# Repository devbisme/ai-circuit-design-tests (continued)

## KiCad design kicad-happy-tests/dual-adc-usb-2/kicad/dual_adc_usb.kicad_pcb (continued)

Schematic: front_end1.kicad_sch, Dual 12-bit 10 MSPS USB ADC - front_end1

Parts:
C32: 15pF; C_1206_3216Metric; MPN GRM3195C2A150JA01D
C33: 2.2pF; C_1206_3216Metric; MPN GRM3195C2A2R2CA01D
C34: 10pF; C_0603_1608Metric; MPN GRM1885C1H100JA01D
C35: 3-10pF; C_Trimmer_Murata_TZC3; MPN TZC3Z100A110R00
C36, C38, C42: 100nF; C_0603_1608Metric; MPN GRM188R71C104KA01D
C37, C39, C43: 1uF; C_0603_1608Metric; MPN GRM188R71C105KA12D
C40, C41: 22pF; C_0603_1608Metric; MPN GRM1885C1H220JA01D
C44: 330pF; C_0603_1608Metric; MPN GRM1885C1H331JA01D
D2: BAV99; SOT-23; MPN BAV99
J2: IN_A; BNC_Amphenol_B6252HB-NPP3G-50_Horizontal; MPN B6252HB-NPP3G-50
R19: 909k; R_1206_3216Metric; Tolerance 0.1%; MPN RT1206BRD07909KL
R20: 100k; R_0603_1608Metric; Tolerance 0.1%; MPN RT0603BRD07100KL
R21: 100; R_0603_1608Metric; Tolerance 1%; MPN RC0603FR-07100RL
R22, R23: 1k; R_0603_1608Metric; Tolerance 0.1%; MPN RT0603BRD071KL
R24, R25: 953; R_0603_1608Metric; Tolerance 0.1%; MPN RT0603BRD07953RL
R26, R27: 49.9; R_0603_1608Metric; Tolerance 1%; MPN RC0603FR-0749R9L
U8: OPA810xD; SOIC-8_3.9x4.9mm_P1.27mm; MPN OPA810IDR
U9: THS4521ID; SOIC-8_3.9x4.9mm_P1.27mm; MPN THS4521IDR

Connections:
+3V3A: C36.1, C37.1, D2.2 (A), U8.7 (V+); also elsewhere on the board
+3V3_ADC: C42.1, C43.1, U9.3 (V_{S+}), U9.7 (~PD); also elsewhere on the board
-3V3A: C38.1, C39.1, D2.1 (K), U8.4 (V-); also elsewhere on the board
/front_end1/ATT_A: C33.2, C34.1, C35.1, D2.3 (K), R19.2, R20.1, R21.1
/front_end1/BUF_IN_A: R21.2, U8.3 (+)
/front_end1/BUF_OUT_A: R22.1, U8.2 (-), U8.6
/front_end1/FDA_INN_A: C41.1, R23.2, R25.1, U9.1 (-)
/front_end1/FDA_INP_A: C40.1, R22.2, R24.1, U9.8 (+)
/front_end1/FDA_OUTN_A: C40.2, R24.2, R27.1, U9.5
/front_end1/FDA_OUTP_A: C41.2, R25.2, R26.1, U9.4
/front_end1/VIN_A: C32.1, C33.1, J2.1 (In), R19.1
AIN_AN: C44.2, R27.2; also elsewhere on the board
AIN_AP: C44.1, R26.2; also elsewhere on the board
GND: C32.2, C34.2, C35.2, C36.2, C37.2, C38.2, C39.2, C42.2, C43.2, J2.2 (Ext), R20.2, R23.1, U9.6 (V_{S-}); also elsewhere on the board
VCMA: U9.2 (V_{OCM}); also elsewhere on the board

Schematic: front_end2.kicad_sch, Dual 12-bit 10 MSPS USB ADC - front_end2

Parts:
C45: 15pF; C_1206_3216Metric; MPN GRM3195C2A150JA01D
C46: 2.2pF; C_1206_3216Metric; MPN GRM3195C2A2R2CA01D
C47: 10pF; C_0603_1608Metric; MPN GRM1885C1H100JA01D
C48: 3-10pF; C_Trimmer_Murata_TZC3; MPN TZC3Z100A110R00
C49, C51, C55: 100nF; C_0603_1608Metric; MPN GRM188R71C104KA01D
C50, C52, C56: 1uF; C_0603_1608Metric; MPN GRM188R71C105KA12D
C53, C54: 22pF; C_0603_1608Metric; MPN GRM1885C1H220JA01D
C57: 330pF; C_0603_1608Metric; MPN GRM1885C1H331JA01D
D3: BAV99; SOT-23; MPN BAV99
J3: IN_B; BNC_Amphenol_B6252HB-NPP3G-50_Horizontal; MPN B6252HB-NPP3G-50
R28: 909k; R_1206_3216Metric; Tolerance 0.1%; MPN RT1206BRD07909KL
R29: 100k; R_0603_1608Metric; Tolerance 0.1%; MPN RT0603BRD07100KL
R30: 100; R_0603_1608Metric; Tolerance 1%; MPN RC0603FR-07100RL
R31, R32: 1k; R_0603_1608Metric; Tolerance 0.1%; MPN RT0603BRD071KL
R33, R34: 953; R_0603_1608Metric; Tolerance 0.1%; MPN RT0603BRD07953RL
R35, R36: 49.9; R_0603_1608Metric; Tolerance 1%; MPN RC0603FR-0749R9L
U10: OPA810xD; SOIC-8_3.9x4.9mm_P1.27mm; MPN OPA810IDR
U11: THS4521ID; SOIC-8_3.9x4.9mm_P1.27mm; MPN THS4521IDR

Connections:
+3V3A: C49.1, C50.1, D3.2 (A), U10.7 (V+); also elsewhere on the board
+3V3_ADC: C55.1, C56.1, U11.3 (V_{S+}), U11.7 (~PD); also elsewhere on the board
-3V3A: C51.1, C52.1, D3.1 (K), U10.4 (V-); also elsewhere on the board
/front_end2/ATT_B: C46.2, C47.1, C48.1, D3.3 (K), R28.2, R29.1, R30.1
/front_end2/BUF_IN_B: R30.2, U10.3 (+)
/front_end2/BUF_OUT_B: R31.1, U10.2 (-), U10.6
/front_end2/FDA_INN_B: C54.1, R32.2, R34.1, U11.1 (-)
/front_end2/FDA_INP_B: C53.1, R31.2, R33.1, U11.8 (+)
/front_end2/FDA_OUTN_B: C53.2, R33.2, R36.1, U11.5
/front_end2/FDA_OUTP_B: C54.2, R34.2, R35.1, U11.4
/front_end2/VIN_B: C45.1, C46.1, J3.1 (In), R28.1
AIN_BN: C57.2, R36.2; also elsewhere on the board
AIN_BP: C57.1, R35.2; also elsewhere on the board
GND: C45.2, C47.2, C48.2, C49.2, C50.2, C51.2, C52.2, C55.2, C56.2, J3.2 (Ext), R29.2, R32.1, U11.6 (V_{S-}); also elsewhere on the board
VCMB: U11.2 (V_{OCM}); also elsewhere on the board

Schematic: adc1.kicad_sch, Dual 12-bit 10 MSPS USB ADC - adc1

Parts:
C58, C59: 2.2uF; C_0603_1608Metric; MPN GRM188R61C225KE15D
C60, C64, C68, C69, C70, C71, C73, C74: 100nF; C_0603_1608Metric; MPN GRM188R71C104KA01D
C61, C65: 2.2uF; C_0805_2012Metric; MPN GRM21BR71C225KA12L
C62, C63, C66, C67: 1uF; C_0603_1608Metric; MPN GRM188R71C105KA12D
C72: 10uF; C_0805_2012Metric; MPN GRM21BR61C106KE15L
R37: 20k; R_0603_1608Metric; Tolerance 1%; MPN RC0603FR-0720KL
R38, R39: 10k; R_0603_1608Metric; Tolerance 1%; MPN RC0603FR-0710KL
U12: LTC2291IUP; QFN-64-1EP_9x9mm_P0.5mm_EP7.15x7.15mm; MPN LTC2291IUP#PBF

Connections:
+3V3: C73.1, C74.1, U12.32 (OVDD), U12.49 (OVDD); also elsewhere on the board
+3V3_ADC: C68.1, C69.1, C70.1, C71.1, C72.1, R37.1, U12.7 (VDD), U12.10 (VDD), U12.18 (VDD), U12.19 (SENSEB), U12.21 (MUX), U12.62 (SENSEA), U12.63 (VDD); also elsewhere on the board
/adc1/ADC_MODE: R37.2, R38.1, U12.60 (MODE)
/adc1/REFHA: C60.1, C61.1, C62.1, U12.3 (REFHA), U12.4 (REFHA)
/adc1/REFHB: C64.1, C65.1, C66.1, U12.13 (REFHB), U12.14 (REFHB)
/adc1/REFLA: C60.2, C61.2, C63.1, U12.5 (REFLA), U12.6 (REFLA)
/adc1/REFLB: C64.2, C65.2, C67.1, U12.11 (REFLB), U12.12 (REFLB)
ADC_CLK: U12.8 (CLKA), U12.9 (CLKB); also elsewhere on the board
ADC_SHDN: R39.1, U12.22 (SHDNB), U12.59 (SHDNA); also elsewhere on the board
AIN_AN: U12.2 (AINA-); also elsewhere on the board
AIN_AP: U12.1 (AINA+); also elsewhere on the board
AIN_BN: U12.15 (AINB-); also elsewhere on the board
AIN_BP: U12.16 (AINB+); also elsewhere on the board
DA0: U12.43 (DA0); also elsewhere on the board
DA1: U12.44 (DA1); also elsewhere on the board
DA2: U12.45 (DA2); also elsewhere on the board
DA3: U12.46 (DA3); also elsewhere on the board
DA4: U12.47 (DA4); also elsewhere on the board
DA5: U12.48 (DA5); also elsewhere on the board
DA6: U12.51 (DA6); also elsewhere on the board
DA7: U12.52 (DA7); also elsewhere on the board
DA8: U12.53 (DA8); also elsewhere on the board
DA9: U12.54 (DA9); also elsewhere on the board
DA10: U12.55 (DA10); also elsewhere on the board
DA11: U12.56 (DA11); also elsewhere on the board
DB0: U12.26 (DB0); also elsewhere on the board
DB1: U12.27 (DB1); also elsewhere on the board
DB2: U12.28 (DB2); also elsewhere on the board
DB3: U12.29 (DB3); also elsewhere on the board
DB4: U12.30 (DB4); also elsewhere on the board
DB5: U12.33 (DB5); also elsewhere on the board
DB6: U12.34 (DB6); also elsewhere on the board
DB7: U12.35 (DB7); also elsewhere on the board
DB8: U12.36 (DB8); also elsewhere on the board
DB9: U12.37 (DB9); also elsewhere on the board
DB10: U12.38 (DB10); also elsewhere on the board
DB11: U12.39 (DB11); also elsewhere on the board
GND: C58.2, C59.2, C62.2, C63.2, C66.2, C67.2, C68.2, C69.2, C70.2, C71.2, C72.2, C73.2, C74.2, R38.2, R39.2, U12.17 (GND), U12.23 (~OEB), U12.31 (OGND), U12.50 (OGND), U12.58 (~OEA), U12.64 (GND), U12.65 (GND); also elsewhere on the board
OFA: U12.57 (OFA); also elsewhere on the board
OFB: U12.40 (OFB); also elsewhere on the board
VCMA: C58.1, U12.61 (VCMA); also elsewhere on the board
VCMB: C59.1, U12.20 (VCMB); also elsewhere on the board

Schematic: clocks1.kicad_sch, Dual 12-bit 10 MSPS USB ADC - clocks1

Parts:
C75, C76: 100nF; C_0603_1608Metric; MPN GRM188R71C104KA01D
R40: 22; R_0603_1608Metric; Tolerance 1%; MPN RC0603FR-0722RL
R41, R42: 33; R_0603_1608Metric; Tolerance 1%; MPN RC0603FR-0733RL
Y2: 10MHz; Oscillator_SMD_Abracon_ASE-4Pin_3.2x2.5mm; MPN ASE-10.000MHZ-LC-T
Y3: 25MHz; Oscillator_SMD_Abracon_ASE-4Pin_3.2x2.5mm; MPN ASE-25.000MHZ-LC-T

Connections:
+3V3: C75.1, C76.1, Y2.1 (EN), Y2.4 (Vdd), Y3.1 (EN), Y3.4 (Vdd); also elsewhere on the board
/clocks1/XO10_OUT: R40.1, R41.1, Y2.3 (OUT)
/clocks1/XO25_OUT: R42.1, Y3.3 (OUT)
ADC_CLK: R40.2; also elsewhere on the board
FPGA_ADC_CLK: R41.2; also elsewhere on the board
GND: C75.2, C76.2, Y2.2 (GND), Y3.2 (GND); also elsewhere on the board
SYSCLK: R42.2; also elsewhere on the board

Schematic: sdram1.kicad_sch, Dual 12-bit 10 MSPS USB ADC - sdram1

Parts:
C77, C78, C79, C80, C81, C82, C83: 100nF; C_0603_1608Metric; MPN GRM188R71C104KA01D
C84: 10uF; C_0805_2012Metric; MPN GRM21BR61C106KE15L
U13: IS42S16400J-7TL; TSOP-II-54_22.2x10.16mm_P0.8mm; MPN IS42S16400J-7TL

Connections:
+3V3: C77.1, C78.1, C79.1, C80.1, C81.1, C82.1, C83.1, C84.1, U13.1 (VDD), U13.3 (VDDQ), U13.9 (VDDQ), U13.14 (VDD), U13.27 (VDD), U13.43 (VDDQ), U13.49 (VDDQ); also elsewhere on the board
GND: C77.2, C78.2, C79.2, C80.2, C81.2, C82.2, C83.2, C84.2, U13.6 (GNDQ), U13.12 (GNDQ), U13.28 (GND), U13.41 (GND), U13.46 (GNDQ), U13.52 (GNDQ), U13.54 (GND); also elsewhere on the board
SD_A0: U13.23 (A0); also elsewhere on the board
SD_A1: U13.24 (A1); also elsewhere on the board
SD_A2: U13.25 (A2); also elsewhere on the board
SD_A3: U13.26 (A3); also elsewhere on the board
SD_A4: U13.29 (A4); also elsewhere on the board
SD_A5: U13.30 (A5); also elsewhere on the board
SD_A6: U13.31 (A6); also elsewhere on the board
SD_A7: U13.32 (A7); also elsewhere on the board
SD_A8: U13.33 (A8); also elsewhere on the board
SD_A9: U13.34 (A9); also elsewhere on the board
SD_A10: U13.22 (A10); also elsewhere on the board
SD_A11: U13.35 (A11); also elsewhere on the board
SD_BA0: U13.20 (BA0); also elsewhere on the board
SD_BA1: U13.21 (BA1); also elsewhere on the board
SD_CAS_N: U13.17 (~CAS); also elsewhere on the board
SD_CKE: U13.37 (CKE); also elsewhere on the board
SD_CLK: U13.38 (CLK); also elsewhere on the board
SD_CS_N: U13.19 (~CS); also elsewhere on the board
SD_DQ0: U13.2 (DQ0); also elsewhere on the board
SD_DQ1: U13.4 (DQ1); also elsewhere on the board
SD_DQ2: U13.5 (DQ2); also elsewhere on the board
SD_DQ3: U13.7 (DQ3); also elsewhere on the board
SD_DQ4: U13.8 (DQ4); also elsewhere on the board
SD_DQ5: U13.10 (DQ5); also elsewhere on the board
SD_DQ6: U13.11 (DQ6); also elsewhere on the board
SD_DQ7: U13.13 (DQ7); also elsewhere on the board
SD_DQ8: U13.42 (DQ8); also elsewhere on the board
SD_DQ9: U13.44 (DQ9); also elsewhere on the board
SD_DQ10: U13.45 (DQ10); also elsewhere on the board
SD_DQ11: U13.47 (DQ11); also elsewhere on the board
SD_DQ12: U13.48 (DQ12); also elsewhere on the board
SD_DQ13: U13.50 (DQ13); also elsewhere on the board
SD_DQ14: U13.51 (DQ14); also elsewhere on the board
SD_DQ15: U13.53 (DQ15); also elsewhere on the board
SD_DQMH: U13.39 (UDQM); also elsewhere on the board
SD_DQML: U13.15 (LDQM); also elsewhere on the board
SD_RAS_N: U13.18 (~RAS); also elsewhere on the board
SD_WE_N: U13.16 (~WE); also elsewhere on the board

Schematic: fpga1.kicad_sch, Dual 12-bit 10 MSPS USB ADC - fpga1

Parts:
C85, C86, C87, C88, C90, C91, C92, C93, C94, C95, C96, C97, C101, C103, C104: 100nF; C_0603_1608Metric; MPN GRM188R71C104KA01D
C89, C98, C99, C100, C102: 10uF; C_0805_2012Metric; MPN GRM21BR61C106KE15L
D4, D5: RED; LED_0603_1608Metric; MPN LTST-C191KRKT
J4: GPIO; PinHeader_2x05_P2.54mm_Vertical; MPN 61301021121
R43, R44: 100; R_0603_1608Metric; Tolerance 1%; MPN RC0603FR-07100RL
R45, R46, R47, R48, R49, R50: 10k; R_0603_1608Metric; Tolerance 1%; MPN RC0603FR-0710KL
R51, R52: 1k; R_0603_1608Metric; Tolerance 1%; MPN RC0603FR-071KL
U14: ICE40HX4K-TQ144; TQFP-144_20x20mm_P0.5mm; MPN ICE40HX4K-TQ144
U15: W25Q32JVSS; SOIC-8_5.3x5.3mm_P1.27mm; MPN W25Q32JVSSIQ

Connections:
+1V2: C85.1, C86.1, C87.1, C88.1, C89.1, R43.1, R44.1, U14.27 (VCC), U14.40 (VCC), U14.92 (VCC), U14.111 (VCC); also elsewhere on the board
+3V3: C90.1, C91.1, C92.1, C93.1, C94.1, C95.1, C96.1, C97.1, C98.1, C99.1, C104.1, J4.9, R45.1, R46.1, R47.1, R48.1, R49.1, R50.1, U14.6 (VCCIO_3), U14.30 (VCCIO_3), U14.46 (VCCIO_2), U14.57 (VCCIO_2), U14.72 (VCC_SPI), U14.89 (VCCIO_1), U14.100 (VCCIO_1), U14.108 (VPP_2V5), U14.123 (VCCIO_0), U14.131 (VCCIO_0), U15.8 (VCC); also elsewhere on the board
/fpga1/FLASH_HOLD_N: R50.2, U15.7 (~HOLD/~RESET/IO_{3})
/fpga1/FLASH_WP_N: R49.2, U15.3 (~WP/IO_{2})
/fpga1/GNDPLL0: C100.2, C101.2, U14.53 (GNDPLL0)
/fpga1/GNDPLL1: C102.2, C103.2, U14.127 (GNDPLL1)
/fpga1/GPIO0: J4.1, U14.129 (IOT_198_GBIN0)
/fpga1/GPIO1: J4.2, U14.130 (IOT_206)
/fpga1/GPIO2: J4.3, U14.134 (IOT_212)
/fpga1/GPIO3: J4.4, U14.135 (IOT_213)
/fpga1/GPIO4: J4.5, U14.136 (IOT_214)
/fpga1/GPIO5: J4.6, U14.137 (IOT_215)
/fpga1/GPIO6: J4.7, U14.138 (IOT_216)
/fpga1/GPIO7: J4.8, U14.139 (IOT_217)
/fpga1/LED0: R51.1, U14.120 (IOT_179)
/fpga1/LED1: R52.1, U14.121 (IOT_181)
/fpga1/N$71: D4.2 (A), R51.2
/fpga1/N$72: D5.2 (A), R52.2
/fpga1/VCCPLL0: C100.1, C101.1, R43.2, U14.54 (VCCPLL0)
/fpga1/VCCPLL1: C102.1, C103.1, R44.2, U14.126 (VCCPLL1)
ADC_SHDN: U14.25 (IOL_18A); also elsewhere on the board
ANA_EN: U14.38 (IOB_57); also elsewhere on the board
ANA_PG_N: U14.37 (IOB_56); also elsewhere on the board
CFG_CDONE: R45.2, U14.65 (CDONE); also elsewhere on the board
CFG_CRESET: R46.2, U14.66 (~CRESET); also elsewhere on the board
CFG_CS: R48.2, U14.71 (IOB_108_SS), U15.1 (~CS); also elsewhere on the board
CFG_MISO: U14.68 (IOB_106_SDI), U15.2 (DO/IO_{1}); also elsewhere on the board
CFG_MOSI: U14.67 (IOB_105_SDO), U15.5 (DI/IO_{0}); also elsewhere on the board
CFG_SCK: R47.2, U14.70 (IOB_107_SCK), U15.6 (CLK); also elsewhere on the board
DA0: U14.17 (IOL_12A); also elsewhere on the board
DA1: U14.16 (IOL_10B); also elsewhere on the board
DA2: U14.15 (IOL_10A); also elsewhere on the board
DA3: U14.12 (IOL_8B); also elsewhere on the board
DA4: U14.11 (IOL_8A); also elsewhere on the board
DA5: U14.10 (IOL_5B); also elsewhere on the board
DA6: U14.1 (IOL_2A); also elsewhere on the board
DA7: U14.2 (IOL_2B); also elsewhere on the board
DA8: U14.3 (IOL_3A); also elsewhere on the board
DA9: U14.4 (IOL_3B); also elsewhere on the board
DA10: U14.7 (IOL_4A); also elsewhere on the board
DA11: U14.8 (IOL_4B); also elsewhere on the board
DB0: U14.28 (IOL_23A); also elsewhere on the board
DB1: U14.29 (IOL_23B); also elsewhere on the board
DB2: U14.32 (IOL_24B); also elsewhere on the board
DB3: U14.33 (IOL_25A); also elsewhere on the board
DB4: U14.34 (IOL_25B); also elsewhere on the board
DB5: U14.31 (IOL_24A); also elsewhere on the board
DB6: U14.26 (IOL_18B); also elsewhere on the board
DB7: U14.24 (IOL_17B); also elsewhere on the board
DB8: U14.23 (IOL_17A); also elsewhere on the board
DB9: U14.22 (IOL_14B); also elsewhere on the board
DB10: U14.20 (IOL_13B_GBIN7); also elsewhere on the board
DB11: U14.19 (IOL_13A); also elsewhere on the board
FPGA_ADC_CLK: U14.21 (IOL_14A_GBIN6); also elsewhere on the board
FT_ACBUS0: U14.122 (IOT_190); also elsewhere on the board
FT_ACBUS1: U14.124 (IOT_191); also elsewhere on the board
FT_ACBUS2: U14.125 (IOT_192); also elsewhere on the board
FT_ACBUS3: U14.128 (IOT_197_GBIN1); also elsewhere on the board
FT_D0: U14.55 (IOB_91); also elsewhere on the board
FT_D1: U14.52 (IOB_82_GBIN4); also elsewhere on the board
FT_D2: U14.48 (IOB_80); also elsewhere on the board
FT_D3: U14.45 (IOB_73); also elsewhere on the board
FT_D4: U14.44 (IOB_72); also elsewhere on the board
FT_D5: U14.43 (IOB_71); also elsewhere on the board
FT_D6: U14.42 (IOB_64); also elsewhere on the board
FT_D7: U14.41 (IOB_63); also elsewhere on the board
FT_PWREN_N: U14.64 (IOB_104_CBSEL1); also elsewhere on the board
FT_RD_N: U14.61 (IOB_96); also elsewhere on the board
FT_RXF_N: U14.39 (IOB_61); also elsewhere on the board
FT_SIWU_N: U14.63 (IOB_103_CBSEL0); also elsewhere on the board
FT_SUSPEND_N: U14.56 (IOB_94); also elsewhere on the board
FT_TXE_N: U14.60 (IOB_95); also elsewhere on the board
FT_WR_N: U14.62 (IOB_102); also elsewhere on the board
GND: C85.2, C86.2, C87.2, C88.2, C89.2, C90.2, C91.2, C92.2, C93.2, C94.2, C95.2, C96.2, C97.2, C98.2, C99.2, C104.2, D4.1 (K), D5.1 (K), J4.10, U14.5 (GND), U14.13 (GND), U14.14 (GND), U14.59 (GND), U14.69 (GND), U14.86 (GND), U14.103 (GND), U14.132 (GND), U14.140 (GND), U15.4 (GND); also elsewhere on the board
OFA: U14.9 (IOL_5A); also elsewhere on the board
OFB: U14.18 (IOL_12B); also elsewhere on the board
SD_A0: U14.76 (IOR_112); also elsewhere on the board
SD_A1: U14.75 (IOR_111); also elsewhere on the board
SD_A2: U14.74 (IOR_110); also elsewhere on the board
SD_A3: U14.73 (IOR_109); also elsewhere on the board
SD_A4: U14.78 (IOR_114); also elsewhere on the board
SD_A5: U14.79 (IOR_115); also elsewhere on the board
SD_A6: U14.81 (IOR_117); also elsewhere on the board
SD_A7: U14.83 (IOR_119); also elsewhere on the board
SD_A8: U14.84 (IOR_120); also elsewhere on the board
SD_A9: U14.87 (IOR_136); also elsewhere on the board
SD_A10: U14.80 (IOR_116); also elsewhere on the board
SD_A11: U14.90 (IOR_138); also elsewhere on the board
SD_BA0: U14.85 (IOR_128); also elsewhere on the board
SD_BA1: U14.82 (IOR_118); also elsewhere on the board
SD_CAS_N: U14.94 (IOR_141_GBIN2); also elsewhere on the board
SD_CKE: U14.93 (IOR_140_GBIN3); also elsewhere on the board
SD_CLK: U14.95 (IOR_144); also elsewhere on the board
SD_CS_N: U14.88 (IOR_137); also elsewhere on the board
SD_DQ0: U14.119 (IOT_178); also elsewhere on the board
SD_DQ1: U14.118 (IOT_177); also elsewhere on the board
SD_DQ2: U14.117 (IOT_174); also elsewhere on the board
SD_DQ3: U14.115 (IOT_172); also elsewhere on the board
SD_DQ4: U14.114 (IOT_171); also elsewhere on the board
SD_DQ5: U14.110 (IOT_168); also elsewhere on the board
SD_DQ6: U14.105 (IOR_165); also elsewhere on the board
SD_DQ7: U14.101 (IOR_160); also elsewhere on the board
SD_DQ8: U14.99 (IOR_152); also elsewhere on the board
SD_DQ9: U14.102 (IOR_161); also elsewhere on the board
SD_DQ10: U14.104 (IOR_164); also elsewhere on the board
SD_DQ11: U14.106 (IOR_166); also elsewhere on the board
SD_DQ12: U14.107 (IOR_167); also elsewhere on the board
SD_DQ13: U14.112 (IOT_169); also elsewhere on the board
SD_DQ14: U14.113 (IOT_170); also elsewhere on the board
SD_DQ15: U14.116 (IOT_173); also elsewhere on the board
SD_DQMH: U14.96 (IOR_146); also elsewhere on the board
SD_DQML: U14.98 (IOR_148); also elsewhere on the board
SD_RAS_N: U14.91 (IOR_139); also elsewhere on the board
SD_WE_N: U14.97 (IOR_147); also elsewhere on the board
SYSCLK: U14.49 (IOB_81_GBIN5); also elsewhere on the board

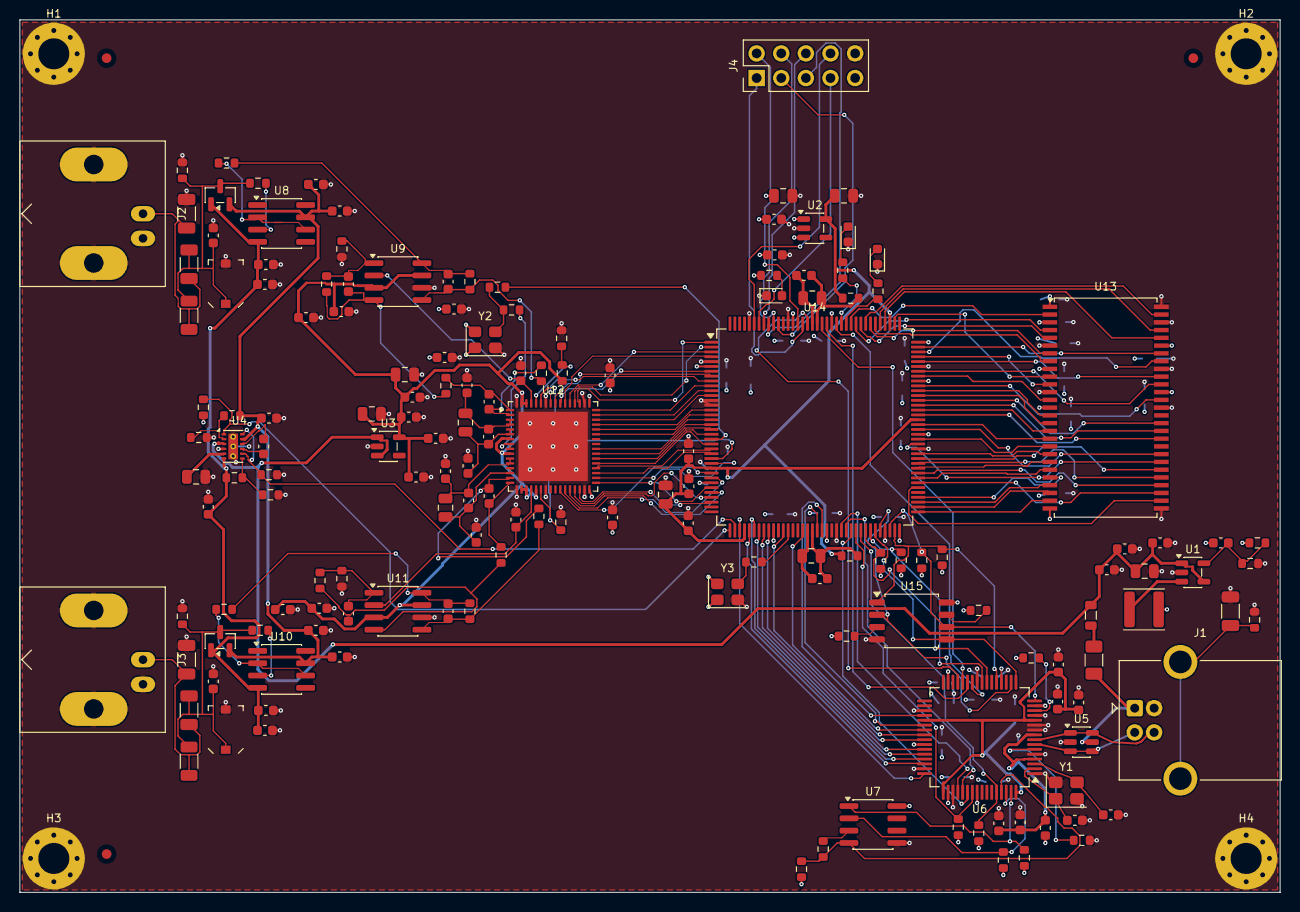
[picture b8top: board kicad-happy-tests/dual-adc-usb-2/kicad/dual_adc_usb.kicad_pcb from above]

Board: 4 copper layers, 130.0 x 90.0 mm, 197 parts (32 on the bottom side), 172 nets.

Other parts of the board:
FID1, FID2, FID3, FID4, FID5, FID6: Fiducial; Fiducial_1mm_Mask2mm
H1, H2, H3, H4: MountingHole; MountingHole_3.2mm_M3_Pad_Via

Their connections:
GND: H1.1, H2.1, H3.1, H4.1; also elsewhere on the board

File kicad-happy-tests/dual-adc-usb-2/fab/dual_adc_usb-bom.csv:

"Refs","Value","Footprint","MPN","Tolerance","Dielectric","Qty"
"C1,C5,C17,C18,C20-C22,C24-C28,C31,C36,C38,C42,C49,C51,C55,C60,C64,C68-C71,C73-C83,C85-C88,C90-C97,C101,C103,C104","100nF","Capacitor_SMD:C_0603_1608Metric","GRM188R71C104KA01D","","X7R","51"
"C2","6.8pF","Capacitor_SMD:C_0603_1608Metric","GRM1885C1H6R8DA01D","","C0G","1"
"C3,C11,C16,C19,C23","4.7uF","Capacitor_SMD:C_0805_2012Metric","GRM21BR71C475KE51L","","X7R","5"
"C4","22uF","Capacitor_SMD:C_0805_2012Metric","GRM21BR61A226ME44L","","X5R","1"
"C6,C9,C72,C84,C89,C98-C100,C102","10uF","Capacitor_SMD:C_0805_2012Metric","GRM21BR61C106KE15L","","X5R","9"
"C7,C8,C10,C37,C39,C43,C50,C52,C56,C62,C63,C66,C67","1uF","Capacitor_SMD:C_0603_1608Metric","GRM188R71C105KA12D","","X7R","13"
"C12-C14,C58,C59","2.2uF","Capacitor_SMD:C_0603_1608Metric","GRM188R61C225KE15D","","X5R","5"
"C15","4.7nF","Capacitor_SMD:C_1206_3216Metric","GRM31BR72J472KW01L","","X7R","1"
"C29,C30","27pF","Capacitor_SMD:C_0603_1608Metric","GRM1885C1H270JA01D","","C0G","2"
"C32,C45","15pF","Capacitor_SMD:C_1206_3216Metric","GRM3195C2A150JA01D","","C0G","2"
"C33,C46","2.2pF","Capacitor_SMD:C_1206_3216Metric","GRM3195C2A2R2CA01D","","C0G","2"
"C34,C47","10pF","Capacitor_SMD:C_0603_1608Metric","GRM1885C1H100JA01D","","C0G","2"
"C35,C48","3-10pF","Capacitor_SMD:C_Trimmer_Murata_TZC3","TZC3Z100A110R00","","","2"
"C40,C41,C53,C54","22pF","Capacitor_SMD:C_0603_1608Metric","GRM1885C1H220JA01D","","C0G","4"
"C44,C57","330pF","Capacitor_SMD:C_0603_1608Metric","GRM1885C1H331JA01D","","C0G","2"
"C61,C65","2.2uF","Capacitor_SMD:C_0805_2012Metric","GRM21BR71C225KA12L","","X7R","2"
"D1","GRN","LED_SMD:LED_0603_1608Metric","LTST-C191KGKT","","","1"
"D2,D3","BAV99","Package_TO_SOT_SMD:SOT-23","BAV99","","","2"
"D4,D5","RED","LED_SMD:LED_0603_1608Metric","LTST-C191KRKT","","","2"
"F1","500mA","Fuse:Fuse_1206_3216Metric","MF-MSMF050-2","","","1"
"FB1","120R@100MHz 2A","Inductor_SMD:L_0805_2012Metric","BLM21PG121SN1D","","","1"
"FB2","600R@100MHz","Inductor_SMD:L_0603_1608Metric","BLM18KG601SN1D","","","1"
"J1","USB_B","Connector_USB:USB_B_OST_USB-B1HSxx_Horizontal","USB-B1HSW6","","","1"
"J2","IN_A","Connector_Coaxial:BNC_Amphenol_B6252HB-NPP3G-50_Horizontal","B6252HB-NPP3G-50","","","1"
"J3","IN_B","Connector_Coaxial:BNC_Amphenol_B6252HB-NPP3G-50_Horizontal","B6252HB-NPP3G-50","","","1"
"J4","GPIO","Connector_PinHeader_2.54mm:PinHeader_2x05_P2.54mm_Vertical","61301021121","","","1"
"L1","2.2uH","Inductor_SMD:L_Changjiang_FNR4020S","FNR4020S2R2MT","","","1"
"R1","453k","Resistor_SMD:R_0603_1608Metric","RC0603FR-07453KL","1%","","1"
"R2,R3,R6,R8","100k","Resistor_SMD:R_0603_1608Metric","RC0603FR-07100KL","1%","","4"
"R4,R12,R14-R18,R38,R39,R45-R50","10k","Resistor_SMD:R_0603_1608Metric","RC0603FR-0710KL","1%","","15"
"R5","174k","Resistor_SMD:R_0603_1608Metric","RC0603FR-07174KL","1%","","1"
"R7","169k","Resistor_SMD:R_0603_1608Metric","RC0603FR-07169KL","1%","","1"
"R9,R51,R52","1k","Resistor_SMD:R_0603_1608Metric","RC0603FR-071KL","1%","","3"
"R10","1M","Resistor_SMD:R_0603_1608Metric","RC0603FR-071ML","1%","","1"
"R11","12k","Resistor_SMD:R_0603_1608Metric","RC0603FR-0712KL","1%","","1"
"R13","2.2k","Resistor_SMD:R_0603_1608Metric","RC0603FR-072K2L","1%","","1"
"R19,R28","909k","Resistor_SMD:R_1206_3216Metric","RT1206BRD07909KL","0.1%","","2"
"R20,R29","100k","Resistor_SMD:R_0603_1608Metric","RT0603BRD07100KL","0.1%","","2"
"R21,R30,R43,R44","100","Resistor_SMD:R_0603_1608Metric","RC0603FR-07100RL","1%","","4"
"R22,R23,R31,R32","1k","Resistor_SMD:R_0603_1608Metric","RT0603BRD071KL","0.1%","","4"
"R24,R25,R33,R34","953","Resistor_SMD:R_0603_1608Metric","RT0603BRD07953RL","0.1%","","4"
"R26,R27,R35,R36","49.9","Resistor_SMD:R_0603_1608Metric","RC0603FR-0749R9L","1%","","4"
"R37","20k","Resistor_SMD:R_0603_1608Metric","RC0603FR-0720KL","1%","","1"
"R40","22","Resistor_SMD:R_0603_1608Metric","RC0603FR-0722RL","1%","","1"
"R41,R42","33","Resistor_SMD:R_0603_1608Metric","RC0603FR-0733RL","1%","","2"
"U1","TLV62569DBV","Package_TO_SOT_SMD:SOT-23-5","TLV62569DBVR","","","1"
"U2","AP2112K-1.2","Package_TO_SOT_SMD:SOT-23-5","AP2112K-1.2TRG1","","","1"
"U3","LP5907MFX-3.3","Package_TO_SOT_SMD:SOT-23-5","LP5907MFX-3.3/NOPB","","","1"
"U4","LM27762","Package_SON:WSON-12-1EP_3x2mm_P0.5mm_EP1x2.65_ThermalVias","LM27762DSSR","","","1"
"U5","USBLC6-2SC6","Package_TO_SOT_SMD:SOT-23-6","USBLC6-2SC6","","","1"
"U6","FT2232HL","Package_QFP:LQFP-64_10x10mm_P0.5mm","FT2232HL-REEL","","","1"
"U7","93LC56B","Package_SO:SOIC-8_3.9x4.9mm_P1.27mm","93LC56BT-I/SN","","","1"
"U8,U10","OPA810xD","Package_SO:SOIC-8_3.9x4.9mm_P1.27mm","OPA810IDR","","","2"
"U9,U11","THS4521ID","Package_SO:SOIC-8_3.9x4.9mm_P1.27mm","THS4521IDR","","","2"
"U12","LTC2291IUP","Package_DFN_QFN:QFN-64-1EP_9x9mm_P0.5mm_EP7.15x7.15mm","LTC2291IUP#PBF","","","1"
"U13","IS42S16400J-7TL","Package_SO:TSOP-II-54_22.2x10.16mm_P0.8mm","IS42S16400J-7TL","","","1"
"U14","ICE40HX4K-TQ144","Package_QFP:TQFP-144_20x20mm_P0.5mm","ICE40HX4K-TQ144","","","1"
"U15","W25Q32JVSS","Package_SO:SOIC-8_5.3x5.3mm_P1.27mm","W25Q32JVSSIQ","","","1"
"Y1","12MHz","Crystal:Crystal_SMD_3225-4Pin_3.2x2.5mm","ABM8-12.000MHZ-B2-T","","","1"
"Y2","10MHz","Oscillator:Oscillator_SMD_Abracon_ASE-4Pin_3.2x2.5mm","ASE-10.000MHZ-LC-T","","","1"
"Y3","25MHz","Oscillator:Oscillator_SMD_Abracon_ASE-4Pin_3.2x2.5mm","ASE-25.000MHZ-LC-T","","","1"

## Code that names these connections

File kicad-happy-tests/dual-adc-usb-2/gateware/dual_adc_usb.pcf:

# iCE40HX4K-TQ144 pin constraints for dual_adc_usb (generated by scripts/gen_pcf.py
# from kicad/dual_adc_usb.net; do not edit by hand -- FPGA pins follow the PCB).
set_io adc_shdn 25
set_io ana_en 38
set_io ana_pg_n 37
set_io cfg_cs 71
set_io cfg_miso 68
set_io cfg_mosi 67
set_io cfg_sck 70
set_io da[0] 17
set_io da[1] 16
set_io da[2] 15
set_io da[3] 12
set_io da[4] 11
set_io da[5] 10
set_io da[6] 1
set_io da[7] 2
set_io da[8] 3
set_io da[9] 4
set_io da[10] 7
set_io da[11] 8
set_io db[0] 28
set_io db[1] 29
set_io db[2] 32
set_io db[3] 33
set_io db[4] 34
set_io db[5] 31
set_io db[6] 26
set_io db[7] 24
set_io db[8] 23
set_io db[9] 22
set_io db[10] 20
set_io db[11] 19
set_io fpga_adc_clk 21
set_io ft_acbus[0] 122
set_io ft_acbus[1] 124
set_io ft_acbus[2] 125
set_io ft_acbus[3] 128
set_io ft_d[0] 55
set_io ft_d[1] 52
set_io ft_d[2] 48
set_io ft_d[3] 45
set_io ft_d[4] 44
set_io ft_d[5] 43
set_io ft_d[6] 42
set_io ft_d[7] 41
set_io ft_pwren_n 64
set_io ft_rd_n 61
set_io ft_rxf_n 39
set_io ft_siwu_n 63
set_io ft_suspend_n 56
set_io ft_txe_n 60
set_io ft_wr_n 62
set_io gpio[0] 129
set_io gpio[1] 130
set_io gpio[2] 134
set_io gpio[3] 135
set_io gpio[4] 136
set_io gpio[5] 137
set_io gpio[6] 138
set_io gpio[7] 139
set_io led0 120
set_io led1 121
set_io ofa 9
set_io ofb 18
set_io sd_a[0] 76
set_io sd_a[1] 75
set_io sd_a[2] 74
set_io sd_a[3] 73
set_io sd_a[4] 78
set_io sd_a[5] 79
set_io sd_a[6] 81
set_io sd_a[7] 83
set_io sd_a[8] 84
set_io sd_a[9] 87
set_io sd_a[10] 80
set_io sd_a[11] 90
set_io sd_ba[0] 85
set_io sd_ba[1] 82
set_io sd_cas_n 94
set_io sd_cke 93
set_io sd_clk 95
set_io sd_cs_n 88
set_io sd_dq[0] 119
set_io sd_dq[1] 118
set_io sd_dq[2] 117
set_io sd_dq[3] 115
set_io sd_dq[4] 114
set_io sd_dq[5] 110
set_io sd_dq[6] 105
set_io sd_dq[7] 101
set_io sd_dq[8] 99
set_io sd_dq[9] 102
set_io sd_dq[10] 104
set_io sd_dq[11] 106
set_io sd_dq[12] 107
set_io sd_dq[13] 112
set_io sd_dq[14] 113
set_io sd_dq[15] 116
set_io sd_dqmh 96
set_io sd_dqml 98
set_io sd_ras_n 91
set_io sd_we_n 97
set_io sysclk 49

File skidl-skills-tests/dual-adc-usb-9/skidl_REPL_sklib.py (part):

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
skidl_REPL = SchLib(tool=SKIDL).add_parts(*[
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            Pin(num='S1',name='SHIELD',func=pin_types.PASSIVE,unit=1),
            Pin(num='A1',name='GND',func=pin_types.PASSIVE,unit=1),
            Pin(num='A12',name='GND',func=pin_types.PASSIVE,unit=1),
            Pin(num='B1',name='GND',func=pin_types.PASSIVE,unit=1),
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            Pin(num='41',name='MSBI/SEN',func=pin_types.INPUT,unit=1),
            Pin(num='42',name='OEA/SCLK',func=pin_types.INPUT,unit=1),
            Pin(num='45',name='STPD/SDATA',func=pin_types.INPUT,unit=1),
            Pin(num='50',name='INA',func=pin_types.INPUT,unit=1),
            Pin(num='51',name='~{INA}',func=pin_types.INPUT,unit=1),
            Pin(num='52',name='CM',func=pin_types.OUTPUT,unit=1),
            Pin(num='53',name='REFT',func=pin_types.PASSIVE,unit=1),
            Pin(num='54',name='REFB',func=pin_types.PASSIVE,unit=1),
            Pin(num='56',name='INT/~{EXT}',func=pin_types.INPUT,unit=1),
            Pin(num='60',name='ISET',func=pin_types.PASSIVE,unit=1),
            Pin(num='62',name='~{INB}',func=pin_types.INPUT,unit=1),
            Pin(num='63',name='INB',func=pin_types.INPUT,unit=1),
            Pin(num='9',name='OVRB',func=pin_types.OUTPUT,unit=1),
            Pin(num='10',name='D0_B',func=pin_types.OUTPUT,unit=1),
            Pin(num='11',name='D1_B',func=pin_types.OUTPUT,unit=1),
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            Pin(num='7',name='DP',func=pin_types.BIDIR,unit=1),
            Pin(num='34',name='~{RESET}',func=pin_types.INPUT,unit=1),
            Pin(num='5',name='REF',func=pin_types.INPUT,unit=1),
            Pin(num='45',name='EECS',func=pin_types.OUTPUT,unit=1),
            Pin(num='44',name='EECLK',func=pin_types.OUTPUT,unit=1),
            Pin(num='43',name='EEDATA',func=pin_types.BIDIR,unit=1),
            Pin(num='1',name='XCSI',func=pin_types.INPUT,unit=1),
            Pin(num='2',name='XCSO',func=pin_types.OUTPUT,unit=1),
            Pin(num='42',name='TEST',func=pin_types.INPUT,unit=1),
            Pin(num='4',name='AGND',func=pin_types.PWRIN,unit=1),
            Pin(num='9',name='AGND',func=pin_types.PWRIN,unit=1),
            Pin(num='3',name='VPHY',func=pin_types.PWRIN,unit=1),
            Pin(num='41',name='AGND',func=pin_types.PWRIN,unit=1),
            Pin(num='8',name='VPLL',func=pin_types.PWRIN,unit=1),
            Pin(num='10',name='GND',func=pin_types.PWRIN,unit=1),
            Pin(num='12',name='VCCIO',func=pin_types.PWRIN,unit=1),
            Pin(num='11',name='GND',func=pin_types.PWRIN,unit=1),
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
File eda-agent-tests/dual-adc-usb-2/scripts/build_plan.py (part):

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conn("LM_CPF", (U, "10"))
conn("+4V", (U, "11"))
C("2.2uF", "+5V", "GND", S)
C("1uF", "LM_CPF", "LM_CN", S, fp="Capacitor_SMD:C_0402_1005Metric")  # flying cap, tight to pins 9/10
C("4.7uF", "LM_CP", "GND", S)
C("2.2uF", "+4V", "GND", S)
C("2.2uF", "-4V", "GND", S)
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

# Bank 3 (left): ADC data, top->bottom; GBIN6 (21) = 10 MHz sample clock.
fpin("FPGA_CLK10", 21)
adc_order = (["ADC_OFA"] + [f"ADC_DA{i}" for i in range(11, -1, -1)]
             + ["ADC_OFB"] + [f"ADC_DB{i}" for i in range(11, -1, -1)])
for net, pin in zip(adc_order, [p for p in bank3 if p != 21]):
    fpin(net, pin)
# Bank 2 (bottom): FT232H FIFO; GBIN4 (52) = 60 MHz CLKOUT.
fpin("FT_CLKOUT", 52)
ft_order = ([f"FT_D{i}" for i in range(8)]
            + ["FT_RXF_N", "FT_TXE_N", "FT_RD_N", "FT_WR_N", "FT_OE_N",
               "FT_SIWU_N", "FT_ACBUS8", "FT_ACBUS9", "LED1_N", "LED2_N"])
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    fpin(net, pin)
for net, pin in zip([f"SD_DQ{i}" for i in range(16)], bank0):
    fpin(net, pin)
fpin("LM_PGOOD_N", [p for p in bank1 if p not in used][0])
spare = [p for p in bank0 + bank1 + bank2 + bank3 if p not in used]

# Power
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
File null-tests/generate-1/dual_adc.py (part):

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# ---------------------------------------------------------------------------
# Pin maps (TQ144). Banks: 0 = top (IOT), 1 = right (IOR), 2 = bottom (IOB),
# 3 = left (IOL). All banks run at 3.3 V.
ADC_PINS = [1, 2, 3, 4, 7, 8, 9, 10, 11, 12, 15, 16, 17,  # OFA, DA11..DA0
            18, 19, 20, 21, 22, 23, 24, 25, 26, 28, 29, 31, 32]  # DB11..DB0, OFB
SDRAM_SIGS = (["DQ0", "DQ1", "DQ2", "DQ3", "DQ4", "DQ5", "DQ6", "DQ7", "LDQM",
               "WE_N", "CAS_N", "RAS_N", "CS_N", "BA0", "BA1", "A10", "A0", "A1",
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             "D6": 80, "D7": 81, "RXF_N": 82, "TXE_N": 83, "RD_N": 84,
             "WR_N": 85, "SIWU_N": 87, "OE_N": 88, "GPIO8": 90, "GPIO9": 91,
             "CLKOUT": 94}  # CLKOUT on GBIN2
CLK10_PIN = 49  # GBIN5
LED_PINS = [37, 38]
GPIO_PINS = [39, 41, 42, 43]
ADC_SHDN_PIN = 44


@subcircuit
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

@subcircuit
def fpga(adc_bus, adc_clk, adc_shdn, sd, fifo, leds, gpio):
    u = Part("FPGA_Lattice", "ICE40HX4K-TQ144", value="ICE40HX4K-TQ144")

    used = set()
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        con(pin, sd[sig])
    for sig, pin in FIFO_PINS.items():
        con(pin, fifo[sig])
    con(CLK10_PIN, adc_clk)
    con(ADC_SHDN_PIN, adc_shdn)
    for pin, net in zip(LED_PINS, leds):
        con(pin, net)
    for pin, net in zip(GPIO_PINS, gpio):
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    hdr[6] += gnd
    for n, h in zip(gpio, gpio_h):  # series protection for off-board signals
        R("100")[1, 2] += n, h
    fpga(fpga_side, fpga_clk, shdn, sd, fifo, leds, gpio)

    # (Mounting holes H1-H4 are added directly in the PCB by make_pcb.py.)

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
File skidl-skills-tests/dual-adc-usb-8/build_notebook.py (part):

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sig.node('esd', 'USBLC6-2SC6  U1\nESD')
sig.node('usb', 'USB-C  J1', fillcolor='#fff4d6')

sig.edge('rc2A', 'adc', label='AIN_A_P/N\n±1.01 V diff')
sig.edge('rc2B', 'adc', label='AIN_B_P/N')
sig.edge('adc', 'fdaA', label='VCM 1.5 V', style='dotted', constraint='false')
sig.edge('adc', 'fdaB', label='VCM', style='dotted', constraint='false')
sig.edge('xo', 'adc', label='ADC_CLK', style='dashed')
sig.edge('xo', 'fpga', label='FPGA_CLK', style='dashed')
sig.edge('adc', 'fpga', label='DA[11:0], DB[11:0]\n@ 40 MSa/s')
sig.edge('fpga', 'ft', label='FT_D[7:0] @ 60 MHz\n≈ 35 MB/s')
sig.edge('ft', 'esd', label='USB_DP/DN\n480 Mb/s')
sig.edge('esd', 'usb')
sig
""")
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
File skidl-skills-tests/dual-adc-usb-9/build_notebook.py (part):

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sig.node('esd', 'USBLC6-2SC6  U1\nESD')
sig.node('usb', 'USB-C  J1', fillcolor='#fff4d6')

sig.edge('rc2A', 'adc', label='AINA_P/N\n±0.90 V diff @ ±10 V')
sig.edge('rc2B', 'adc', label='AINB_P/N')
sig.edge('adc', 'fdaA', label='VCM 1.5 V', style='dotted', constraint='false')
sig.edge('adc', 'fdaB', label='VCM', style='dotted', constraint='false')
sig.edge('xo', 'adc', label='ADC_CLK (33 Ω)', style='dashed')
sig.edge('xo', 'buf', style='dashed')
sig.edge('buf', 'fpga', label='FPGA_CLK40 (33 Ω)', style='dashed')
sig.edge('adc', 'fpga', label='DA[11:0], DB[11:0]\n@ 40 MSa/s')
sig.edge('fpga', 'ft', label='FT_D[7:0] @ 60 MHz\n≈ 35–40 MB/s')
sig.edge('ft', 'esd', label='USB_DP/DM\n480 Mb/s')
sig.edge('esd', 'usb')
sig
""")
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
